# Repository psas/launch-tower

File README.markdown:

PSAS Launch Tower Computer (LTC)
================================

PSAS has had three generations of launch tower computers:

- [LTC v1 (2005-2012)](http://psas.pdx.edu/Lv2LaunchTowerElectronics/)
   - PC-104+ 486 running Linux 2.4 talking CAN to PIC18F-based boards with relays and analog
   - Lucent "Wavelan" PCMCIA WiFi card
   - 12V SLA battery powered with 30W solar panel
   - Metal IP66 case on independent
- [LTC v2 (2012 - 2014)](http://psas.pdx.edu/GroundTeamHome/launch_tower_v2/)
   - Beagle board talking USB to Phidget relay and analog boards
   - Alpha WiFi board
   - Ethernet umbilical cord
   - 12V SLA battery powered with 30W solar panel
   - Medium sized plastic IP67 enclosure
- LTC v3
   - BeagleBone Black using GPIO and analog mounted on a single custom carrier PCB
   - 14.7V LiPo pack with solar charger.
   - Smaller case

This repo contains everything related to the launch tower computer
(LTC), with the exception of the userspace software, which is
contained in the [launch-tower-comm repo](https://github.com/psas/launch-tower-comm).

Contents
========

- doc
   - Documentation, what there is of it.

- eagle
   - Schematics and PCB layouts, made with [Eagle](http://www.cadsoftusa.com/).

- laser_cut_drawings
   - Line art of the power and ignition boards' mounting panels, suitable for use with a laser cutter.

- ltc3
   - Everything related to the design and manufacture of the third generation launch tower computer, LTC3.

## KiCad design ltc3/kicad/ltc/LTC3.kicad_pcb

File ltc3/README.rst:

PSAS Launch Tower Computer III
##############################

This subdirectory contains everything related to the third generation
launch tower computer (LTC3), with the exception of the userspace
software, which is contained in the `launch-tower-comm repo`_.

This is all very much a work in progress.  In fact, we've barely
started; there hasn't been much progress, so far.  Feel free to
contribute as you see fit.

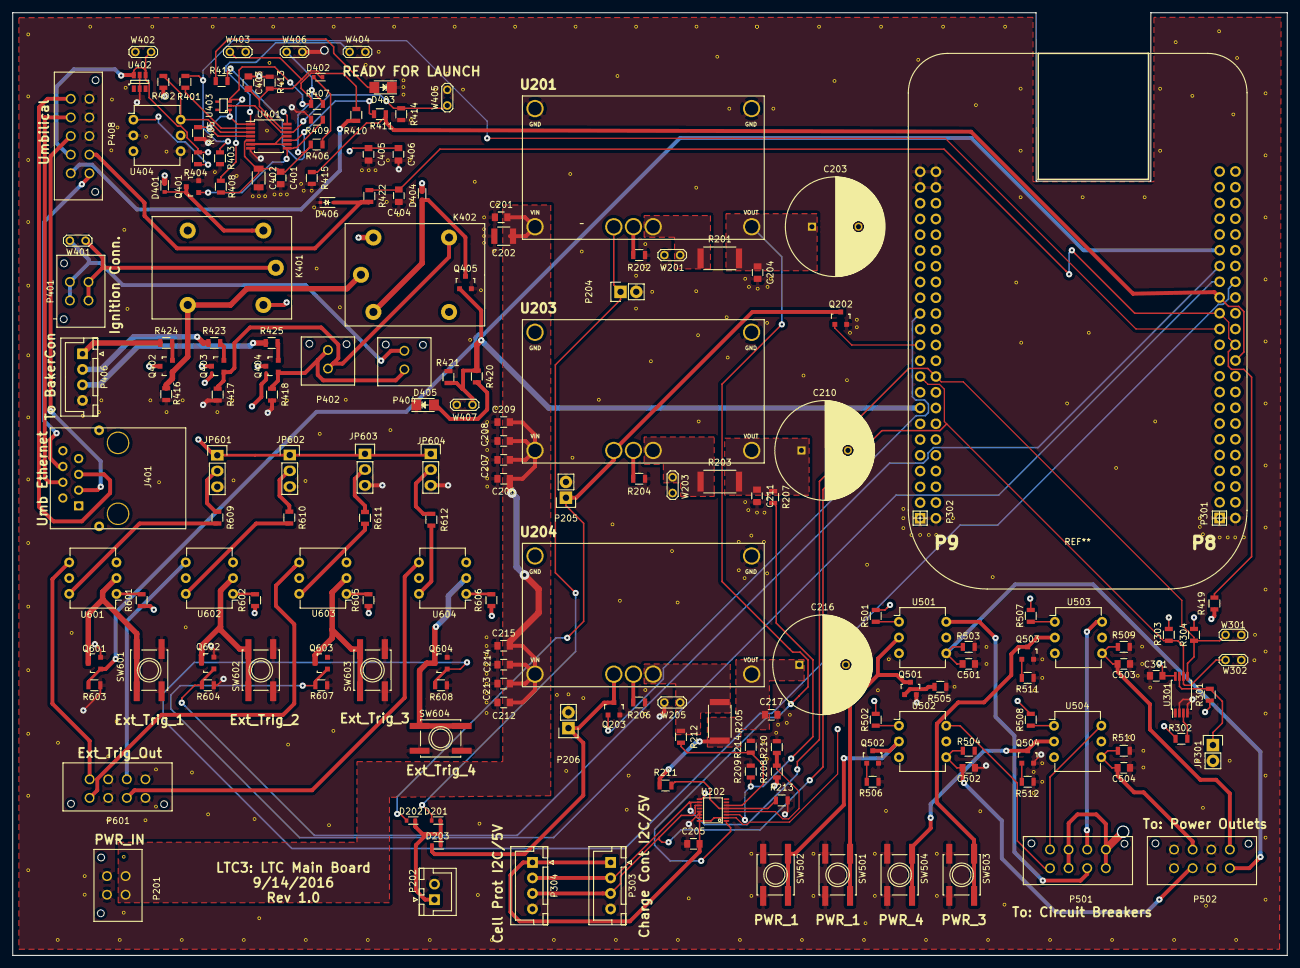
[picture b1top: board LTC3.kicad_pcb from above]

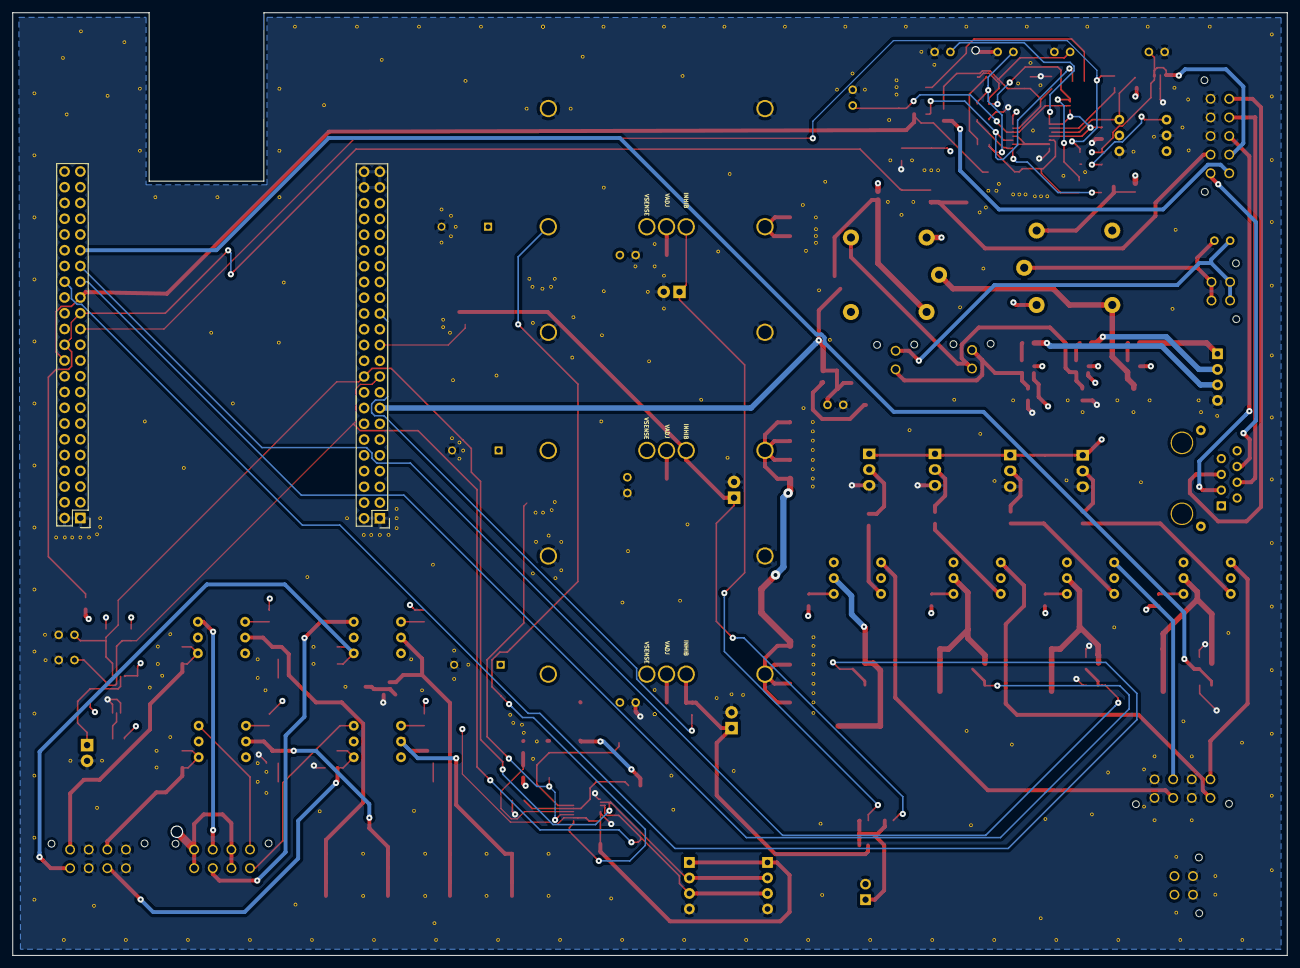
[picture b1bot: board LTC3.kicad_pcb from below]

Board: 4 copper layers, 205.5 x 152.0 mm, 181 parts (2 on the bottom side), 106 nets.

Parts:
C201, C204, C211, C217, C404, C501, C502, C503, C504: 1μ; C_0805
C202: 2.2μ; C_1210
C203, C210, C216: 470μ; C_Radial_D16_L25_P7.5
C205, C301, C403, C405, C406: 0.1μ; C_0805
C206, C207, C208, C209, C212, C213, C214, C215: 4.7μ; C_0805
C401: 10μ; C_0805
C402: NP; C_1206
D201, D202, D203, D401, D402, D404: CDSU4148; SOD-523
D403, D405: RED; LED_1206
D406: 3.3V; SOD-323
J401: RJ45; RJ45_8_SHIELDED
JP301: Pin Head 1x2; Pin_Header_Straight_1x02
JP601, JP602, JP603, JP604: Pin Head 1x3; Pin_Header_Straight_1x03
K401, K402: RELAY_1C; G5LE-14
P201, P401: MicroFit header; Molex_Microfit3_Header_02x02_Straight_43045-0428
P202: XH header; JST_XH_B02B-XH-A_02x2.50mm_Straight
P204, P205, P206: Pin Head 1x2; Pin_Header_Straight_1x02
P301: BeagleBone_Black_Expansion_Header_P8; Pin_Header_Straight_2x23
P302: BeagleBone_Black_Expansion_Header_P9; Pin_Header_Straight_2x23
P303, P304, P406: XH header; JST_XH_B04B-XH-A_04x2.50mm_Straight
P402, P404: MicroFit header; Molex_Microfit3_Header_02x01_Straight_43045-0228
P408: MicroFit header; Molex_Microfit3_Header_02x05_Straight_43045-1028
P501, P502, P601: MicroFit header; Molex_Microfit3_Header_02x04_Straight_43045-0828
Q202, Q203: BSS138; SOT-23
Q401, Q402, Q403, Q404, Q405, Q501, Q502, Q503, Q504, Q601, Q602, Q603, Q604: PMV45EN; SOT-23
R201, R203, R205: 60m; R_2512
R202: 21k; R_0805
R204: 383k; R_0805
R206: 2.87k; R_0805
R207, R208: 20k; R_0805
R209, R210, R213, R214, R402, R405, R409, R414, R416, R417, R418, R421, R505, R506, R511, R512, R603, R604, R607, R608: 10k; R_0805
R211, R212: 36k; R_0805
R301, R302, R303, R304, R410: 5.6k; R_0805
R401, R411: 62k; R_0805
R403, R415: 100k; R_0805
R404: 120; R_0805
R406, R609, R610, R611, R612: 100; R_0805
R407: 500k; R_0805
R408: NP; R_0805
R412, R420: 240; R_0805
R413: 1.5k; R_0805
R419, R422: 5.1k; R_0805
R423, R424, R425: 0; R_0805
R501, R502, R507, R508, R601, R602, R605, R606: 270; R_0805
R503, R504, R509, R510: 51k; R_0805
SW501, SW502, SW503, SW504, SW601, SW602, SW603, SW604: MOMENTARY; SW_SPST_EVQQ2
U201: PTN78020W
U202: LTC2991; MSOP-16
U203, U204: PTN78020H; PTN78020W
U301: CAT24C256; TSSOP-8_4.4x3mm_Pitch0.65mm
U401: CD74HC14; TSSOP-14_4.4x5mm_Pitch0.65mm
U402: SN65220DBV; SOT-23-6
U403: SN74AHC1G08; SC-70-5
U404, U501, U502, U503, U504, U601, U602, U603, U604: TLP3542; DIP-6_W7.62mm
W201, W203, W205, W301, W302, W401, W402, W403, W404, W405, W406, W407: TEST; Test_Point_2Pads

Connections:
+5V: C205.1, C301.1, C405.1, C406.1, D401.1, D404.1, JP601.1, JP602.1, JP603.1, JP604.1, K401.2, K402.2, P302.5, P302.6, P303.1, P304.1, Q402.3, Q403.3, Q404.3, R201.1, R301.1, R302.1, R303.1, R304.1, R402.1, R419.1, R501.1, R502.1, R507.1, R508.1, R601.1, R602.1, R605.1, R606.1, U201.5, U202.2, U202.16, U301.8, U401.14, W201.2
+12V: P501.1, P501.3, P501.5, P501.7, R203.1, R208.1, U203.5, W203.2
+19V: P408.1, R205.1, R212.1, R410.2, U204.5, W205.2
/BeagleBone Black Cape/12V_ENn: P302.23, Q202.1
/BeagleBone Black Cape/19V_ENn: P302.27, Q203.1
/BeagleBone Black Cape/BQ_EEPROM: P301.22, P301.29, R411.2, R415.1
/BeagleBone Black Cape/EXT_PWR_EN_4: C404.1, P301.24, P301.27, R419.2, R422.1
/BeagleBone Black Cape/EXT_TRG_EN_1: P301.35, Q601.1, R603.1
/BeagleBone Black Cape/EXT_TRG_EN_2: P301.33, Q602.1, R604.1
/BeagleBone Black Cape/EXT_TRG_EN_3: P301.31, Q603.1, R607.1
/BeagleBone Black Cape/EXT_TRG_EN_4: P301.32, Q604.1, R608.1
/BeagleBone Black Cape/I2C_CLOCK: P302.19, P303.3, P304.3, R303.2, U202.11, U301.6, W302.1
/BeagleBone Black Cape/I2C_DATA: P302.20, P303.2, P304.2, R304.2, U202.10, U301.5, W301.1
/BeagleBone Black Cape/ROCKET_IGNITE: P302.15, Q405.1, R420.1, R421.1, W407.1
/BeagleBone Black Cape/ROCKET_READYn: P301.25, R401.1, R403.2
/DC-DC Converters/5V_SENSE_H: C203.1, C204.1, R201.2, U201.6, U202.1
/DC-DC Converters/12V_SENSE_H: R207.2, R209.1, U202.3
/DC-DC Converters/12V_SENSE_L: R208.2, R210.1, U202.4
/DC-DC Converters/12V_VOUT: C210.1, C211.1, R203.2, R207.1, U203.6
/DC-DC Converters/19V_SENSE_H: R211.2, R213.1, U202.5
/DC-DC Converters/19V_SENSE_L: R212.2, R214.1, U202.6
/DC-DC Converters/19V_VOUT: C216.1, C217.1, R205.2, R211.1, U204.6
/External Device Power/EXT_POW_1_OPTO_RELAY_P: P501.2, U501.6
/External Device Power/EXT_POW_2_OPTO_RELAY_P: P501.4, U502.6
/External Device Power/EXT_POW_3_OPTO_RELAY_P: P501.6, U503.6
/External Device Power/EXT_POW_4_OPTO_RELAY_P: P501.8, U504.6
/External Device Power/EXT_PWR_1_OUT: C501.1, P502.1, R503.1, U501.4
/External Device Power/EXT_PWR_2_OUT: C502.1, P502.3, R504.1, U502.4
/External Device Power/EXT_PWR_3_OUT: C503.1, P502.5, R509.1, U503.4
/External Device Power/EXT_PWR_4_OUT: C504.1, P502.7, R510.1, U504.4
/External Device Power/EXT_PWR_EN_1: Q501.1, R505.1
/External Device Power/EXT_PWR_EN_2: Q502.1, R506.1
/External Device Power/EXT_PWR_EN_3: Q503.1, R511.1
/External Device Power/EXT_PWR_EN_4: Q504.1, R512.1
/External Device Triggers/EXT_TRG_1_OUT: P601.1, U601.4
/External Device Triggers/EXT_TRG_2_OUT: P601.3, U602.4
/External Device Triggers/EXT_TRG_3_OUT: P601.5, U603.4
/External Device Triggers/EXT_TRG_4_OUT: P601.7, U604.4
/Rocket Umbilical & Ignition Control/IGN_BATT_P: K401.1, P401.1, P401.2, W401.2
/Rocket Umbilical & Ignition Control/ROCKET_ETH_1: J401.3, P408.3
/Rocket Umbilical & Ignition Control/ROCKET_ETH_2: J401.4, P408.4
/Rocket Umbilical & Ignition Control/ROCKET_ETH_3: J401.5, P408.5
/Rocket Umbilical & Ignition Control/ROCKET_ETH_4: J401.6, P408.6
/Rocket Umbilical & Ignition Control/ROCKET_READY_5V: P408.2, R404.2, U402.4, U402.6, W402.1
/Rocket Umbilical & Ignition Control/UMB_CONN_FROM_RKT: D406.1, P408.7, R422.2
GND: C201.2, C202.2, C203.2, C204.2, C205.2, C206.2, C207.2, C208.2, C209.2, C210.2, C211.2, C212.2, C213.2, C214.2, C215.2, C216.2, C217.2, C301.2, C401.2, C402.2, C403.2, C404.2, C405.2, C406.2, C501.2, C502.2, C503.2, C504.2, D403.1, D405.1, D406.2, JP301.2, JP601.3, JP602.3, JP603.3, JP604.3, P201.3, P201.4, P202.2, P204.2, P205.2, P206.2, P301.1, P301.2, P302.1, P302.2, P302.43, P302.44, P302.45, P302.46, P303.4, P304.4, P406.4, P408.8, P408.9, P408.10, P502.2, P502.4, P502.6, P502.8, P601.2, P601.4, P601.6, P601.8, Q202.2, Q203.2, Q401.2, Q405.2, Q501.2, Q502.2, Q503.2, Q504.2, Q601.2, Q602.2, Q603.2, Q604.2, R202.2, R204.2, R206.2, R209.2, R210.2, R213.2, R214.2, R403.1, R405.2, R409.2, R413.2, R414.2, R415.2, R416.2, R417.2, R418.2, R421.2, R503.2, R504.2, R505.2, R506.2, R509.2, R510.2, R511.2, R512.2, R603.2, R604.2, R607.2, R608.2, SW501.2, SW502.2, SW503.2, SW504.2, SW601.2, SW602.2, SW603.2, SW604.2, U201.1, U201.7, U202.9, U202.13, U202.14, U202.15, U203.1, U203.7, U204.1, U204.7, U301.1, U301.2, U301.4, U401.7, U402.2, U402.5, U404.2, U404.4, W201.1, W203.1, W205.1, W301.2, W302.2, W402.2, W403.2, W404.2, W405.2, W406.2, W407.2
GND_IGN: P401.3, P401.4, P404.2, W401.1
unnamed: C401.1, C402.1, R406.1, R407.1, R408.1, U401.5, W406.1
unnamed: C403.1, R410.1, R413.1, U401.13, W403.1
unnamed: D201.1, D202.1, D203.1, P202.1
unnamed: D201.2, P204.1, U201.3
unnamed: D202.2, P205.1, Q202.3, U203.3
unnamed: D203.2, P206.1, Q203.3, U204.3
unnamed: D401.2, K401.5, Q401.3
unnamed: D402.1, R407.2, R408.2, U403.3
unnamed: D402.2, R406.2
unnamed: D403.2, R412.2
unnamed: D404.2, K402.5, Q405.3
unnamed: D405.2, R420.2
unnamed: JP301.1, R301.2, U301.7
unnamed: JP601.2, R609.1
unnamed: JP602.2, R610.1
unnamed: JP603.2, R611.1
unnamed: JP604.2, R612.1
unnamed: K401.3, K402.1, Q402.1, R416.1
unnamed: K402.3, P402.1, Q403.1, R417.1
unnamed: P402.2, P404.1, Q404.1, R418.1
unnamed: P406.1, R424.2
unnamed: P406.2, R423.2
unnamed: P406.3, R425.2
unnamed: Q401.1, R409.1, U401.8
unnamed: Q402.2, R424.1
unnamed: Q403.2, R423.1
unnamed: Q404.2, R425.1
unnamed: Q501.3, SW501.1, U501.2
unnamed: Q502.3, SW502.1, U502.2
unnamed: Q503.3, SW503.1, U503.2
unnamed: Q504.3, SW504.1, U504.2
unnamed: Q601.3, SW601.1, U601.2
unnamed: Q602.3, SW602.1, U602.2
unnamed: Q603.3, SW603.1, U603.2
unnamed: Q604.3, SW604.1, U604.2
unnamed: R202.1, U201.4
unnamed: R204.1, U203.4
unnamed: R206.1, U204.4
unnamed: R302.2, U301.3
unnamed: R401.2, U401.2
unnamed: R402.2, U401.3, U404.6
unnamed: R404.1, U404.1
unnamed: R405.1, U401.1, U401.4, U403.1, W404.1
unnamed: R411.1, R412.1, U401.10
unnamed: R414.1, U401.12, U403.2, W405.1
unnamed: R501.2, U501.1
unnamed: R502.2, U502.1
unnamed: R507.2, U503.1
unnamed: R508.2, U504.1
unnamed: R601.2, U601.1
unnamed: R602.2, U602.1
unnamed: R605.2, U603.1
unnamed: R606.2, U604.1
unnamed: R609.2, U601.6
unnamed: R610.2, U602.6
unnamed: R611.2, U603.6
unnamed: R612.2, U604.6
unnamed: U401.6, U401.9, U401.11
VBATT: C201.1, C202.1, C206.1, C207.1, C208.1, C209.1, C212.1, C213.1, C214.1, C215.1, P201.1, P201.2, U201.2, U203.2, U204.2

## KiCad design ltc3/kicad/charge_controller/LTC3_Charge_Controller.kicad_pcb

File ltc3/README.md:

# PSAS Launch Tower Computer III

This subdirectory contains everything related to the third generation
launch tower computer (LTC3), with the exception of the userspace
software, which is contained in the [launch-tower-comm][1] repo.

[1]: https://github.com/psas/launch-tower-comm

For a quick introduction to the project, read the [Requirements
doc][2] at `./doc/requirements/LTC3_Requirements_Spec.adoc`

[2]: https://github.com/psas/launch-tower/blob/master/ltc3/doc/requirements/LTC3_Requirements_Spec.adoc

This is all very much a work in progress!  Feel free to contribute as
you see fit.

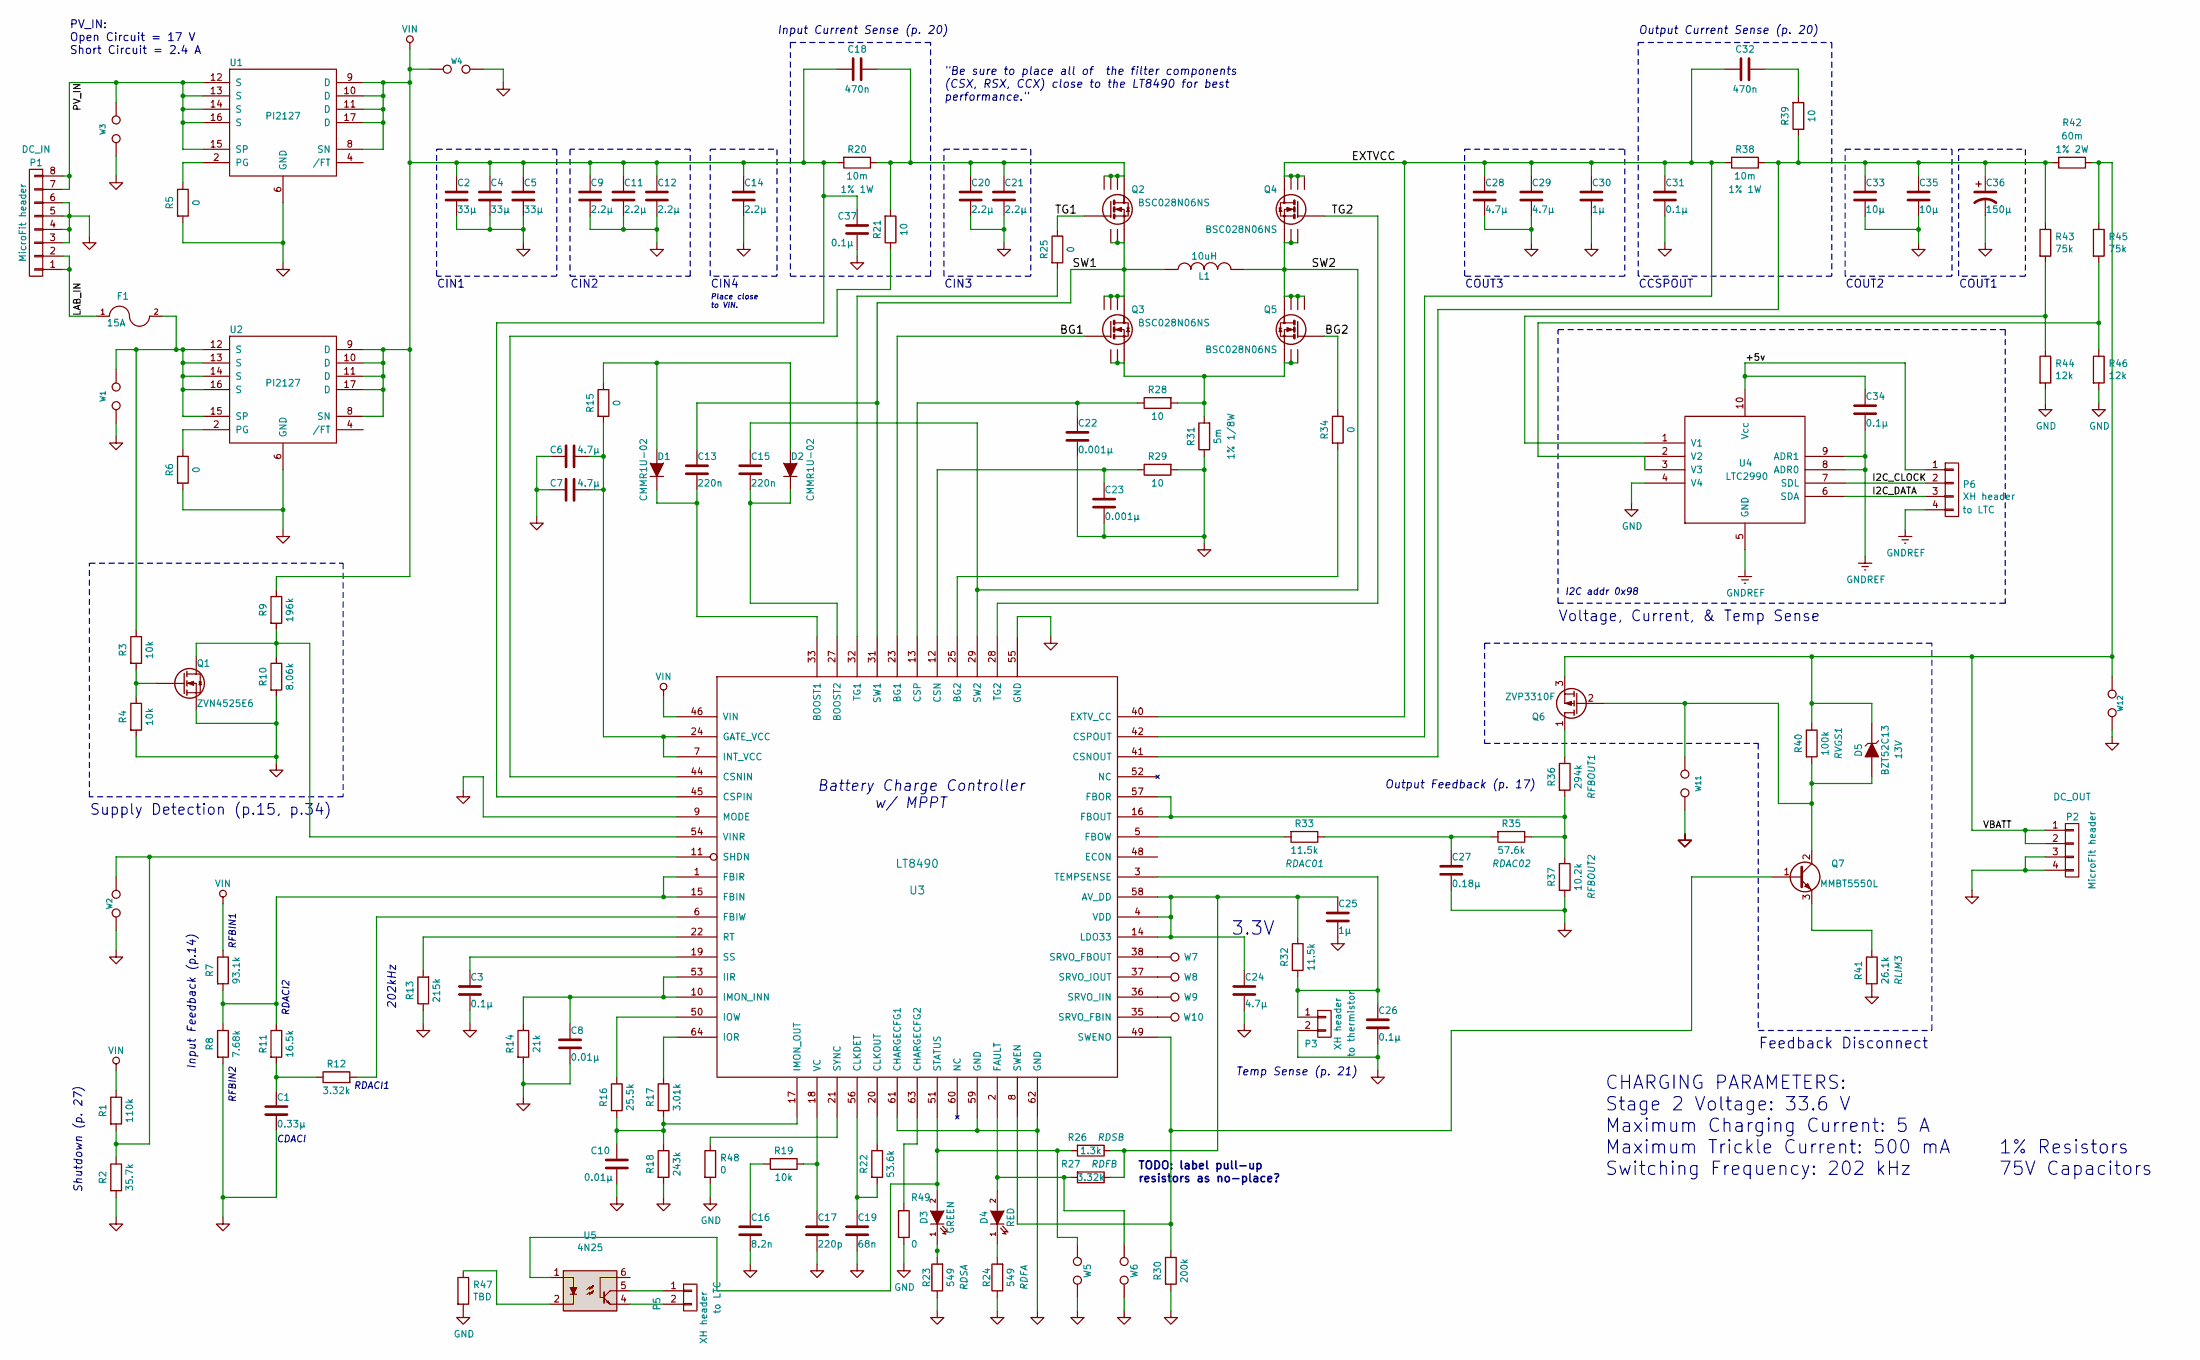
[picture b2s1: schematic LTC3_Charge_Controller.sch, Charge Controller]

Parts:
C1: 0.33μ; C_0805; Mfg_PN GRM21AR72A334KAC5L
C2, C4, C5: 33μ; c_elec_10x10; Mfg_PN UUX2A330MNL1GS
C3, C26, C31: 0.1μ; C_0805; Mfg_PN GCM21BR72A104KA37L
C6, C7, C24: 4.7μ; C_0805; Mfg_PN GRM21BR71C475KA73L
C8, C10: 0.01μ; C_0805; Mfg_PN GRM216R71H103JA01D
C9, C11, C12, C14, C20, C21: 2.2μ; C_1210; Mfg_PN GRM32ER72A225KA35L
C13, C15: 220n; C_0805; Mfg_PN GRM21BR71H224KA01L
C16: 8.2n; C_0805; Mfg_PN GRM21BR71H823KA01L
C17: 220p; C_0805; Mfg_PN CC0805KRX7R9BB221
C18, C32: 470n; C_0805; Mfg_PN GRM21BR71H474KA88L
C19: 68n; C_0805; Mfg_PN GRM219R71E683KA01D
C22, C23: 0.001μ; C_0805; Mfg_PN GRM216R71H102JA01D
C25: 1μ; C_0805; Mfg_PN GRM21BR71E105KA99K
C27: 0.18μ; C_0805; Mfg_PN GRM21BR71H184KA01L
C28, C29: 4.7μ; C_2220; Mfg_PN GRM55ER72A475KA01L
C30: 1μ; C_0805; Mfg_PN GRJ21BC72A105KE11L
C33, C35: 10μ; c_elec_6.3x7.7; Mfg_PN UCD1K100MCL1GS
C34: 0.1μ; C_0805; Mfg_PN GRM21BR71E104KA01L
C36: 150μ; C_Radial_D12.5_L25_P5; Mfg_PN UPW2A151MHD
C37: 0.1μ; C_0805; Mfg_PN GRM21BR71H104KA01L
D1, D2: CMMR1U-02; SOD-123; Mfg_PN CMMR1U-02 TR
D3: GREEN; LED_1206; Mfg_PN LTST-C150GKT
D4: RED; LED_1206; Mfg_PN LTST-C150CKT
D5: BZT52C13; SOD-123; Mfg_PN BZT52C13-7-F
F1: 15A; Fuseholder_Auto_Blade_Regular_Keystone_3557-2; Mfg_PN 3557-2
L1: 10uH; Coilcraft_SER2900; Mfg_PN SER2915L-103KL
P1: MicroFit header; Molex_Microfit3_Header_02x04_Straight_43045-0828; Mfg_PN 43045-0828
P2: MicroFit header; Molex_Microfit3_Header_02x02_Straight_43045-0428; Mfg_PN 43045-0428
P3: XH header; JST_XH_B02B-XH-A_02x2.50mm_Straight; Mfg_PN B2B-XH-A(LF)(SN)
P5: XH header; JST_EH_B02B-XH-A_02x2.50mm_Straight; Mfg_PN B2B-XH-A(LF)(SN)
P6: XH header; JST_EH_B04B-XH-A_04x2.50mm_Straight; Mfg_PN B4B-XH-A(LF)(SN)
Q1: ZVN4525E6; SOT-26; Mfg_PN ZVN4525E6TA
Q2, Q3, Q4, Q5: BSC028N06NS; SO-8; Mfg_PN BSC028N06NS
Q6: ZVP3310F; SOT-23; Mfg_PN ZVP3310FTA
Q7: MMBT5550L; SOT-23; Mfg_PN MMBT5550LT1G
R1: 110k; R_0805; Mfg_PN RC0805FR-07110KL
R2: 35.7k; R_0805; Mfg_PN RC0805FR-0735K7L
R3, R4, R19: 10k; R_0805; Mfg_PN RC0805FR-0710KL
R5, R6, R48, R49: 0; R_0805; Mfg_PN RC0805JR-070RL
R7: 93.1k; R_0805; Mfg_PN RC0805FR-0793K1L
R8: 7.68k; R_0805; Mfg_PN RC0805FR-077K68L
R9: 196k; R_0805; Mfg_PN RC0805FR-07196KL
R10: 8.06k; R_0805; Mfg_PN MCR10EZHF8061
R11: 16.5k; R_0805; Mfg_PN RC0805FR-0716K5L
R12, R27: 3.32k; R_0805; Mfg_PN RC0805FR-073K32L
R13: 215k; R_0805; Mfg_PN RC0805FR-07215KL
R14: 21k; R_0805; Mfg_PN RC0805FR-0721KL
R15, R25, R34: 0; R_0603; Mfg_PN RC0603JR-070RL
R16: 25.5k; R_0805; Mfg_PN CRCW080527K1FKTA
R17: 3.01k; R_0805; Mfg_PN RC0805FR-073K01L
R18: 243k; R_0805; Mfg_PN RC0805FR-07243KL
R20, R38: 10m; R_1206; Mfg_PN WSLP1206R0100FEA
R21, R28, R29, R39: 10; R_0805; Mfg_PN RC0805FR-0710RL
R22: 53.6k; R_0805; Mfg_PN RC0805FR-0753K6L
R23, R24: 549; R_0805; Mfg_PN RC0805FR-07549RL
R26: 1.3k; R_0805; Mfg_PN RC0805FR-071K3L
R30: 200k; R_0805; Mfg_PN RC0805FR-07200KL
R31: 5m; R_1206; Mfg_PN WSL12065L000FEA
R32, R33: 11.5k; R_0805; Mfg_PN RC0805FR-0711K5L
R35: 57.6k; R_0805; Mfg_PN RC0805FR-0757K6L
R36: 294k; R_0805; Mfg_PN RC0805FR-07294KL
R37: 10.2k; R_0805; Mfg_PN RC0805FR-0710K2L
R40: 100k; R_0805; Mfg_PN RC0805FR-07100KL
R41: 26.1k; R_0805; Mfg_PN RC0805FR-0726K1L
R42: 60m; R_2512; Mfg_PN PE2512FKE7W0R06L
R43, R45: 75k; R_0805; Mfg_PN RC0805FR-0775KL
R44, R46: 12k; R_0805; Mfg_PN RC0805FR-0712KL
R47: TBD; R_0805
U1, U2: PI2127; LGA-17; Mfg_PN PI2127-01-LGIZ
U3: LT8490; Mfg_PN LT8490IUKJ#PBF
U4: LTC2990; MSOP-10; Mfg_PN LTC2990IMS#PBF
U5: 4N25; DIP-6_W7.62mm; Mfg_PN 4N25
W1, W2, W3, W4, W5, W6, W11, W12: TEST; Test_Point_2Pads
W7, W8, W9, W10: TEST_1P; Measurement_Point_Square-SMD-Pad_Small

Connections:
/+5v: C34.1, P6.1, U4.10 (Vcc)
/BG1: Q3.4 (G), U3.23 (BG1)
/BG2: Q5.4 (G), R34.1
/EXTVCC: C28.1, C29.1, C30.1, C31.1, C32.2, Q4.5 (D), Q4.6 (D), Q4.7 (D), Q4.8 (D), R38.2, U3.40 (EXTV_CC), U3.42 (CSPOUT)
/I2C_CLOCK: P6.2, U4.7 (SDL)
/I2C_DATA: P6.3, U4.6 (SDA)
/LAB_IN: F1.1, P1.1, P1.2
/PV_IN: P1.7, P1.8, U1.12 (S), U1.13 (S), U1.14 (S), U1.15 (SP), U1.16 (S), W3.1
/SW1: C13.1, L1.1, Q2.1 (S), Q2.2 (S), Q2.3 (S), Q3.5 (D), Q3.6 (D), Q3.7 (D), Q3.8 (D), U3.31 (SW1)
/SW2: C15.1, L1.2, Q4.1 (S), Q4.2 (S), Q4.3 (S), Q5.5 (D), Q5.6 (D), Q5.7 (D), Q5.8 (D), U3.29 (SW2)
/TG1: Q2.4 (G), R25.1
/TG2: Q4.4 (G), U3.28 (TG2)
/VBATT: D5.1 (K), P2.1, P2.2, Q6.3 (S), R40.1, R42.1, R45.1, W12.1
GND: C1.2, C2.2, C3.2, C4.2, C5.2, C6.2, C7.2, C8.2, C9.2, C10.2, C11.2, C12.2, C14.2, C16.2, C17.2, C19.2, C20.2, C21.2, C22.2, C23.2, C24.2, C25.2, C26.2, C27.2, C28.2, C29.2, C30.2, C31.2, C33.2, C35.2, C36.2, C37.2, P1.3, P1.4, P1.5, P1.6, P2.3, P2.4, P3.2, Q1.4 (S), R2.2, R4.2, R5.2, R6.2, R8.2, R10.2, R13.1, R14.2, R18.2, R23.1, R24.1, R29.2, R30.2, R31.1, R37.2, R41.2, R44.2, R46.2, R47.2, R48.2, R49.2, U1.6 (GND), U2.6 (GND), U3.9 (MODE), U3.55 (GND), U3.59 (GND), U3.61 (CHARGECFG1), U3.62 (GND), U4.4 (V4), W1.1, W2.2, W3.2, W4.2, W5.2, W6.2, W11.2, W12.2
GNDREF: C34.2, P6.4, U4.5 (GND), U4.8 (ADR0), U4.9 (ADR1)
unnamed: C1.1, R11.2, R12.1
unnamed: C3.1, U3.19 (SS)
unnamed: C6.1, C7.1, R15.2, U3.7 (INT_VCC), U3.24 (GATE_VCC)
unnamed: C8.1, R14.1, U3.10 (IMON_INN), U3.53 (IIR)
unnamed: C10.1, R16.2, R17.2, R18.1, U3.17 (IMON_OUT)
unnamed: C13.2, D1.1 (K), U3.33 (BOOST1)
unnamed: C15.2, D2.1 (K), U3.27 (BOOST2)
unnamed: C16.1, R19.2
unnamed: C17.1, R19.1, U3.18 (VC)
unnamed: C18.1, C20.1, C21.1, Q2.5 (D), Q2.6 (D), Q2.7 (D), Q2.8 (D), R20.1, R21.2
unnamed: C19.1, R22.2, U3.56 (CLKDET)
unnamed: C22.1, R28.1, U3.13 (CSP)
unnamed: C23.1, R29.1, U3.12 (CSN)
unnamed: C24.1, C25.1, R26.1, R27.1, R32.1, U3.4 (VDD), U3.14 (LDO33), U3.58 (AV_DD)
unnamed: C26.1, P3.1, R32.2, U3.3 (TEMPSENSE)
unnamed: C27.1, R33.1, R35.2
unnamed: C32.1, R39.2
unnamed: C33.1, C35.1, C36.1, R38.1, R39.1, R42.2, R43.1, U3.41 (CSNOUT)
unnamed: D1.2 (A), D2.2 (A), R15.1
unnamed: D3.1 (K), R23.2
unnamed: D3.2 (A), R26.2, U3.51 (STATUS), U5.1, W5.1
unnamed: D4.1 (K), R24.2
unnamed: D4.2 (A), R27.2, U3.2 (FAULT), W6.1
unnamed: D5.2 (A), Q6.2 (G), Q7.2 (C), R40.2, W11.1
unnamed: F1.2, R3.1, U2.12 (S), U2.13 (S), U2.14 (S), U2.15 (SP), U2.16 (S), W1.2
unnamed: P5.1, U5.5
unnamed: P5.2, U5.4
unnamed: Q1.1 (D), R9.2, R10.1, U3.54 (VINR)
unnamed: Q1.3 (G), R3.2, R4.1
unnamed: Q3.1 (S), Q3.2 (S), Q3.3 (S), Q5.1 (S), Q5.2 (S), Q5.3 (S), R28.2, R31.2
unnamed: Q6.1 (D), R36.1
unnamed: Q7.1 (B), R30.1, U3.8 (SWEN), U3.49 (SWENO)
unnamed: Q7.3 (E), R41.1
unnamed: R1.2, R2.1, U3.11 (SHDN), W2.1
unnamed: R5.1, U1.2 (PG)
unnamed: R6.1, U2.2 (PG)
unnamed: R7.2, R8.1, R11.1, U3.1 (FBIR), U3.15 (FBIN)
unnamed: R12.2, U3.6 (FBIW)
unnamed: R13.2, U3.22 (RT)
unnamed: R16.1, U3.50 (IOW)
unnamed: R17.1, U3.64 (IOR)
unnamed: R21.1, U3.44 (CSNIN)
unnamed: R22.1, U3.20 (CLKOUT)
unnamed: R25.2, U3.32 (TG1)
unnamed: R33.2, U3.5 (FBOW)
unnamed: R34.2, U3.25 (BG2)
unnamed: R35.1, R36.2, R37.1, U3.16 (FBOUT), U3.57 (FBOR)
unnamed: R43.2, R44.1, U4.1 (V1)
unnamed: R45.2, R46.1, U4.2 (V2), U4.3 (V3)
unnamed: R47.1, U5.2
unnamed: R48.1, U3.21 (SYNC)
unnamed: R49.1, U3.63 (CHARGECFG2)
unnamed: U3.35 (SRVO_FBIN), W10.1
unnamed: U3.36 (SRVO_IIN), W9.1
unnamed: U3.37 (SRVO_IOUT), W8.1
unnamed: U3.38 (SRVO_FBOUT), W7.1
VIN: C2.1, C4.1, C5.1, C9.1, C11.1, C12.1, C14.1, C18.2, C37.1, R1.1, R7.1, R9.1, R20.2, U1.8 (SN), U1.9 (D), U1.10 (D), U1.11 (D), U1.17 (D), U2.8 (SN), U2.9 (D), U2.10 (D), U2.11 (D), U2.17 (D), U3.45 (CSPIN), U3.46 (VIN), W4.1

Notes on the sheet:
Place close to VIN.
CIN1
CIN2
CIN3
COUT3
CCSPOUT
COUT2
COUT1
CIN4
RFBIN1
RFBIN2
RDACI1
RDACI2
CDACI
202kHz
Input Feedback (p.14)
Output Feedback (p. 17)
Input Current Sense (p. 20)
Output Current Sense (p. 20)
Shutdown (p. 27)
Temp Sense (p. 21)
Supply Detection (p.15, p.34)
Voltage, Current, & Temp Sense
I2C addr 0x98
PV_IN: Open Circuit = 17 V Short Circuit = 2.4 A
CHARGING PARAMETERS: Stage 2 Voltage: 33.6 V Maximum Charging Current: 5 A Maximum Trickle Current: 500 mA Switching Frequency: 202 kHz
Feedback Disconnect
Battery Charge Controller w/ MPPT
TODO: label pull-up resistors as no-place?
1% Resistors 75V Capacitors
"Be sure to place all of the filter components (CSX, RSX, CCX) close to the LT8490 for best performance."
3.3V

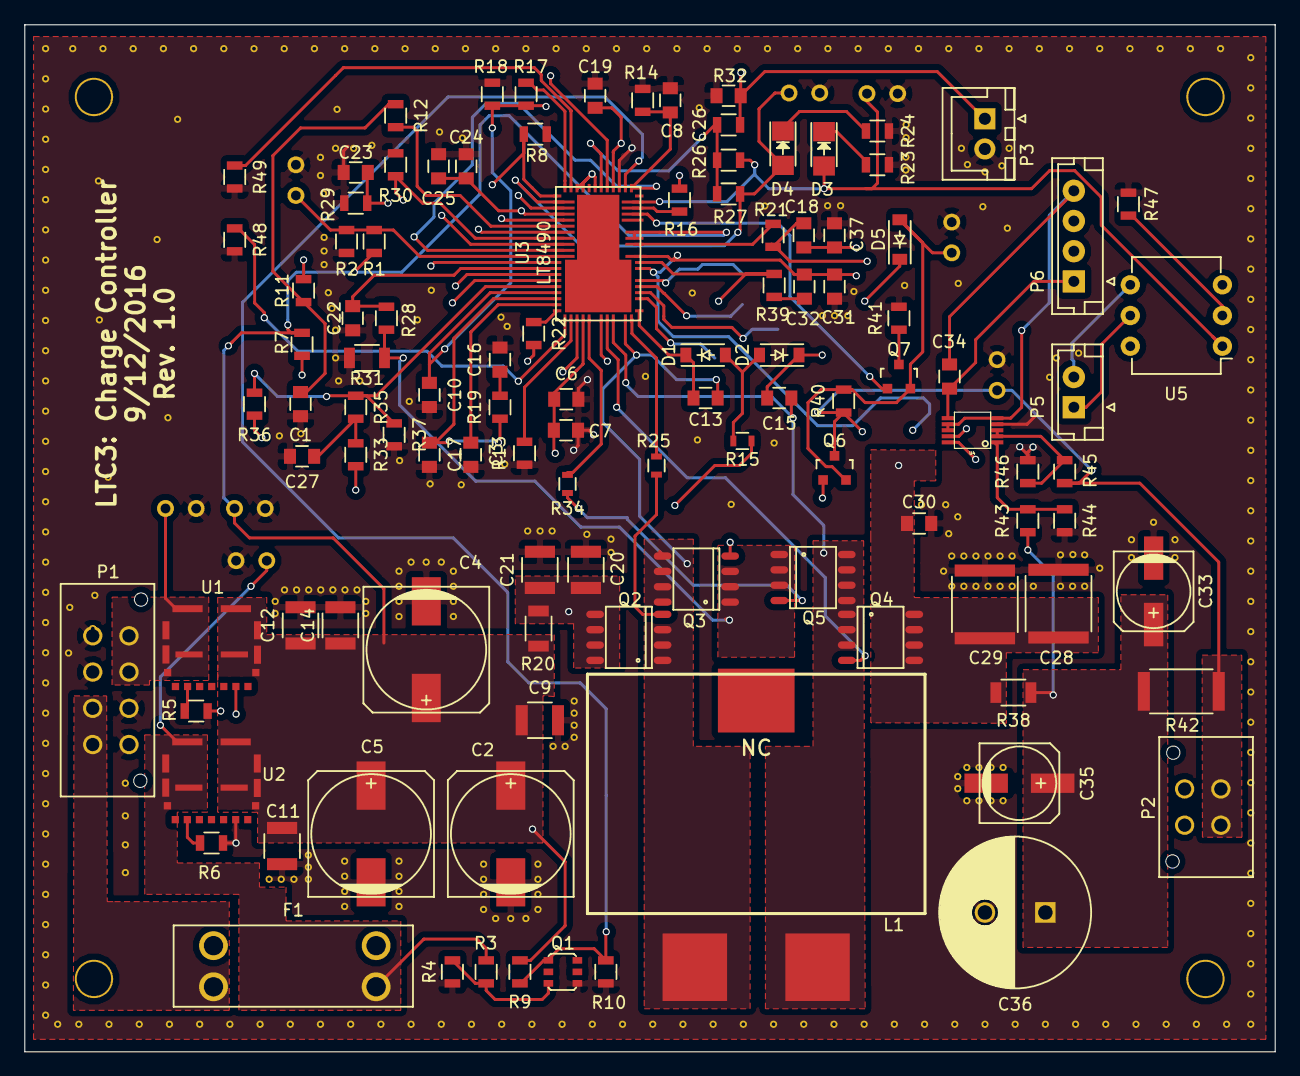
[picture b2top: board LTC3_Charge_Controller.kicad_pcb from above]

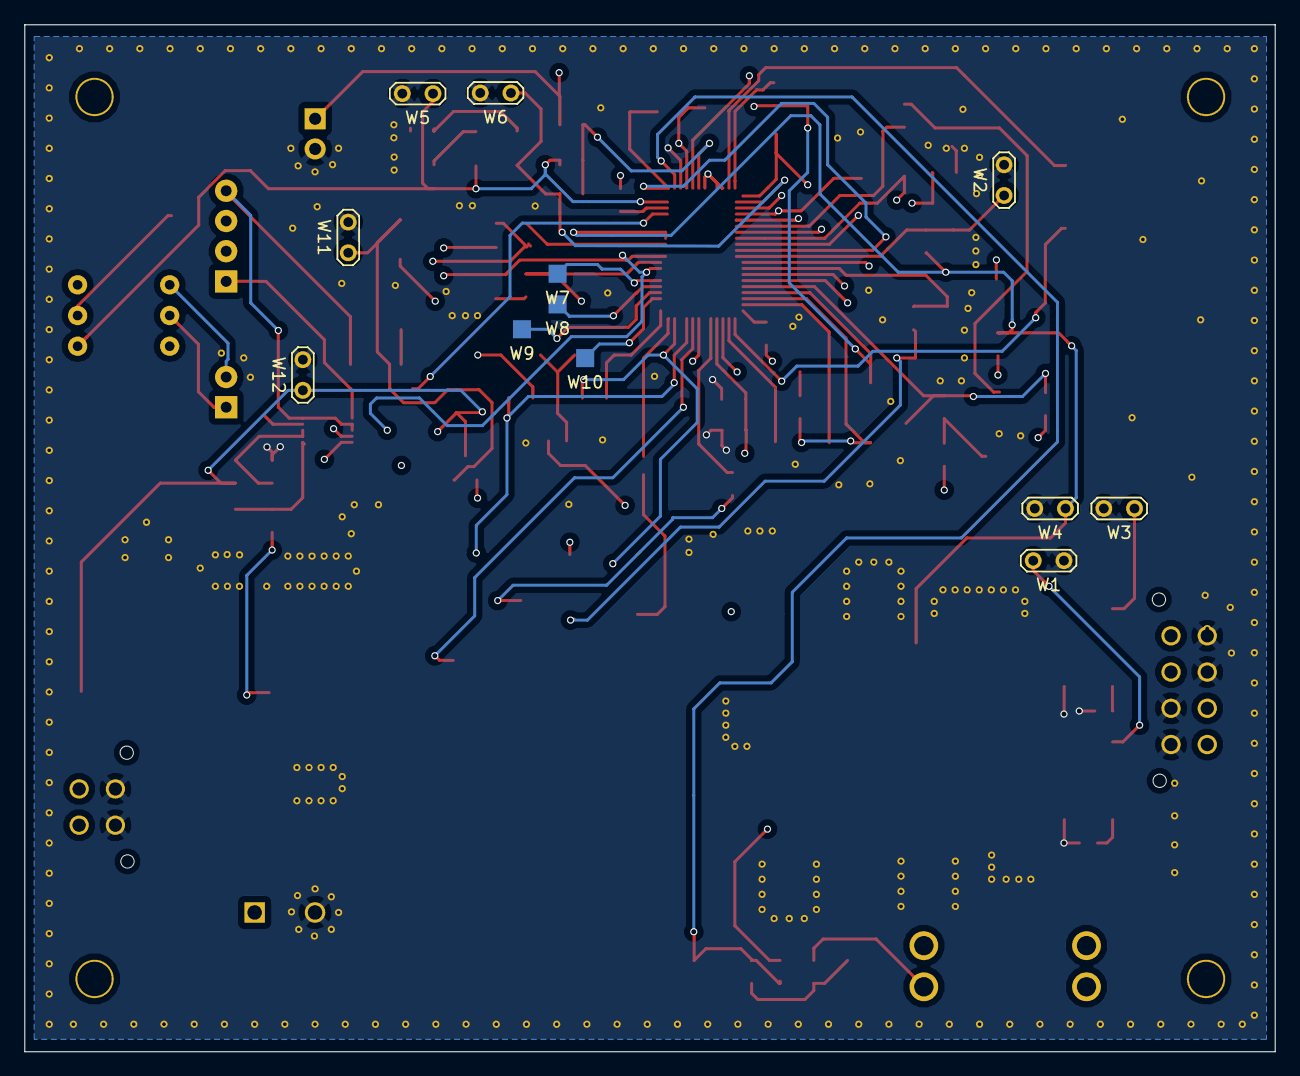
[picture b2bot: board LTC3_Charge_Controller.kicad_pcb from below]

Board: 4 copper layers, 103.5 x 85.0 mm, 122 parts (12 on the bottom side), 72 nets.
